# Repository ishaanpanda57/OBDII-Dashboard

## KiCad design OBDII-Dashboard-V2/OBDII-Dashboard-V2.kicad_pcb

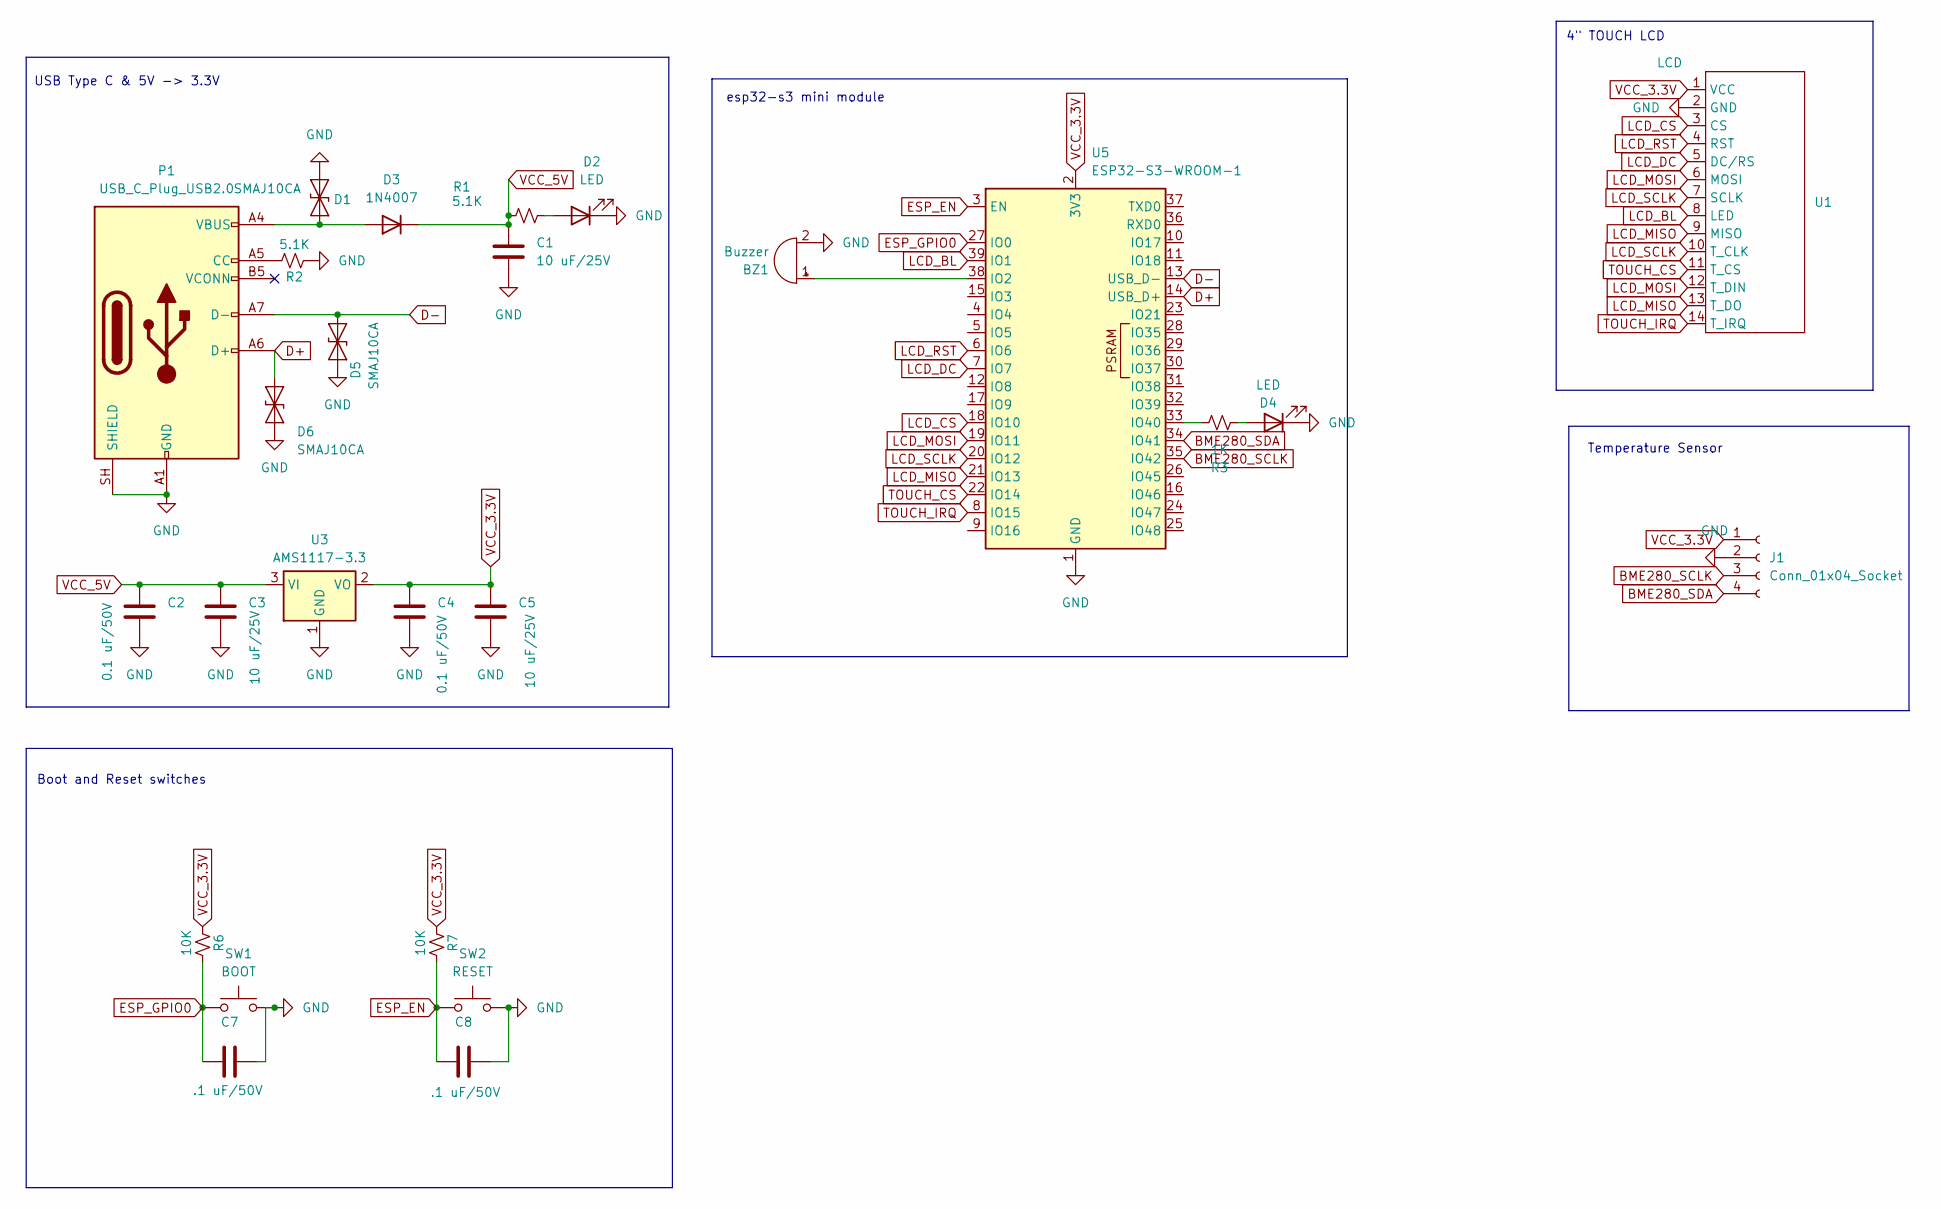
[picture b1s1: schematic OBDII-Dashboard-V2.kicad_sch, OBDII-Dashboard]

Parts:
BZ1: Buzzer; PUIAudio_SMT_0825_S_4_R
C1, C3, C5: 10 uF/25V; C_0805_2012Metric
C2, C4: 0.1 uF/50V; C_0805_2012Metric
C7, C8: .1 uF/50V; C_0805_2012Metric
D1, D5, D6: SMAJ10CA; D_SMA
D2, D4: LED; LED_0805_2012Metric
D3: 1N4007; D_SMA
J1: Conn_01x04_Socket; PinHeader_1x04_P2.54mm_Vertical
P1: USB_C_Plug_USB2.0; USB_C_Receptacle_GCT_USB4105-xx-A_16P_TopMnt_Horizontal
R1, R2: 5.1K; R_0805_2012Metric_Pad1.20x1.40mm_HandSolder
R3: 1K; R_0805_2012Metric_Pad1.20x1.40mm_HandSolder
R6, R7: 10K; R_0805_2012Metric_Pad1.20x1.40mm_HandSolder
SW1: BOOT; SW_Push_1P1T_NO_CK_KSC9xxG
SW2: RESET; SW_Push_1P1T_NO_CK_KSC9xxG
U1: LCD; PinHeader_1x14_P2.54mm_Vertical
U3: AMS1117-3.3; SOT-223-3_TabPin2
U5: ESP32-S3-WROOM-1

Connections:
BME280_SCLK: J1.3, U5.35 (IO42); also elsewhere on the board
BME280_SDA: J1.4, U5.34 (IO41); also elsewhere on the board
D+: D6.2 (A2), P1.A6 (D+), U5.14 (USB_D+)
D-: D5.2 (A2), P1.A7 (D-), U5.13 (USB_D-)
ESP_EN: C8.1, R7.2, SW2.1, U5.3 (EN)
ESP_GPIO0: C7.1, R6.2, SW1.1, U5.27 (IO0)
GND: BZ1.2 (-), C1.2, C2.2, C3.2, C4.2, C5.2, C7.2, C8.2, D1.1 (A1), D2.1 (K), D4.1 (K), D5.1 (A1), D6.1 (A1), J1.2, P1.A1 (GND), P1.A12 (GND), P1.B1 (GND), P1.B12 (GND), P1.SH (SHIELD), R2.1, SW1.2, SW2.2, U1.2 (GND), U3.1 (GND), U5.1 (GND), U5.40 (GND), U5.41 (GND); also elsewhere on the board
LCD_BL: U1.8 (LED), U5.39 (IO1); also elsewhere on the board
LCD_CS: U1.3 (CS), U5.18 (IO10); also elsewhere on the board
LCD_DC: U1.5 (DC/RS), U5.7 (IO7); also elsewhere on the board
LCD_MISO: U1.9 (MISO), U1.13 (T_DO), U5.21 (IO13); also elsewhere on the board
LCD_MOSI: U1.6 (MOSI), U1.12 (T_DIN), U5.19 (IO11); also elsewhere on the board
LCD_RST: U1.4 (RST), U5.6 (IO6); also elsewhere on the board
LCD_SCLK: U1.7 (SCLK), U1.10 (T_CLK), U5.20 (IO12); also elsewhere on the board
unnamed: BZ1.1 (+), U5.38 (IO2)
unnamed: D1.2 (A2), D3.2 (A), P1.A4 (VBUS), P1.A9 (VBUS), P1.B4 (VBUS), P1.B9 (VBUS)
unnamed: D2.2 (A), R1.1
unnamed: D4.2 (A), R3.1
unnamed: P1.A5 (CC), R2.2
unnamed: R3.2, U5.33 (IO40)
TOUCH_CS: U1.11 (T_CS), U5.22 (IO14); also elsewhere on the board
TOUCH_IRQ: U1.14 (T_IRQ), U5.8 (IO15); also elsewhere on the board
VCC_3.3V: C4.1, C5.1, J1.1, R6.1, R7.1, U1.1 (VCC), U3.2 (VO), U5.2 (3V3); also elsewhere on the board
VCC_5V: C1.1, C2.1, C3.1, D3.1 (K), R1.2, U3.3 (VI)

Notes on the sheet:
4" TOUCH LCD
Temperature Sensor
Boot and Reset switches
esp32-s3 mini module
USB Type C & 5V -> 3.3V

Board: 2 copper layers, 26 parts (0 on the bottom side), 24 nets, no tracks yet.

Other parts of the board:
BME280: Conn_01x04_Socket; PinHeader_1x04_P2.54mm_Vertical
LCD: LCD; PinHeader_1x14_P2.54mm_Vertical

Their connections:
BME280_SCLK: BME280.3; also elsewhere on the board
BME280_SDA: BME280.4; also elsewhere on the board
GND: BME280.2, LCD.2 (GND); also elsewhere on the board
LCD_BL: LCD.8 (LED); also elsewhere on the board
LCD_CS: LCD.3 (CS); also elsewhere on the board
LCD_DC: LCD.5 (DC/RS); also elsewhere on the board
LCD_MISO: LCD.9 (MISO), LCD.13 (T_DO); also elsewhere on the board
LCD_MOSI: LCD.6 (MOSI), LCD.12 (T_DIN); also elsewhere on the board
LCD_RST: LCD.4 (RST); also elsewhere on the board
LCD_SCLK: LCD.7 (SCLK), LCD.10 (T_CLK); also elsewhere on the board
TOUCH_CS: LCD.11 (T_CS); also elsewhere on the board
TOUCH_IRQ: LCD.14 (T_IRQ); also elsewhere on the board
VCC_3.3V: BME280.1, LCD.1 (VCC); also elsewhere on the board
